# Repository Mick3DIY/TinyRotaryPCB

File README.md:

<picture>
    
</picture>

# TinyRotaryPCB

A tiny PCB (with surface resistors) for the BOURNS PEC11R rotary encoder.

## Printed Circuit Board (PCB) :

As part of an educational project, the schematic and PCB are made with [KiCad](https://www.kicad.org) version 9 ([kicad](kicad/) folder).

:bulb: All important parameters are stored in the schematic/PCB editors **text variables** (common project variables).

The TinyRotaryPCB itself with the rotary encoder (in reverse side for panel mount), dimensions (mm) :

The panelization option (2x2 boards as separate project) was generated with the KiCad plugin [KiKit](https://github.com/yaqwsx/KiKit), dimensions (mm) in [kicad/panel](kicad/panel/) folder :

If you want a quick and affordable manufacturer for your next electronic project, get a unique 10€ coupon code in <ins>your first order</ins> in [AISLER](https://aisler.net) with my referral code : `MakeInEurope-ECYPW` :heart:

Big thanks to [AISLER](https://aisler.net) PCB manufacturer :eu:

## Code :

The shell script to easily generate panels (in [kicad](kicad/) folder)… :laughing:

```shell
#!/bin/bash
# TinyRotaryPCB with KiCad and KiKit plugin for PCB panelization
# GitHub project : https://github.com/Mick3DIY/TinyRotaryPCB
# KiCad documentation : https://www.kicad.org
# KiKit plugin documentation : https://github.com/yaqwsx/KiKit

# Input and output files
INPUT_FILE="TinyRotaryPCB.kicad_pcb"
OUTPUT_DIR="panel"
OUTPUT_FILE="${OUTPUT_DIR}/TinyRotaryPCB_panel.kicad_pcb"

# Layout parameters, by default 2x2 -> panelize.sh <rows> <cols> parameters
LAYOUT_ROWS="${1:-2}"
LAYOUT_COLS="${2:-2}"
LAYOUT_SPACE="2mm"

# Tab parameters
TAB_TYPE="fixed"
TAB_HWIDTH="2mm"
TAB_VWIDTH="2mm"
TAB_VCOUNT="2"

# Cuts parameters
CUTS="mousebites; drill: 0.5mm; spacing: 0.75mm; offset: -0.3mm; prolong: 0.5mm"

# Framing parameters
FRAME_TYPE="railstb"
FRAME_WIDTH="2mm"
FRAME_SPACE="2mm"

# Text parameters
TEXT_HEIGHT="0.8mm"
TEXT_VOFFSET_POS="1mm"
TEXT_VOFFSET_NEG="-1mm"
TEXT_JUSTIFY="hjustify: center; vjustify: center;"
POST_MILLRADIUS="1mm"

# Ensure output directory exist
mkdir -p "${OUTPUT_DIR}"

# Kikit command with all parameters
kikit panelize \
    --layout "grid; rows: ${LAYOUT_ROWS}; cols: ${LAYOUT_COLS}; space: ${LAYOUT_SPACE}" \
    --tabs "${TAB_TYPE}; hwidth: ${TAB_HWIDTH}; vwidth: ${TAB_VWIDTH}; vcount: ${TAB_VCOUNT}" \
    --cuts "${CUTS}" \
    --framing "${FRAME_TYPE}; width: ${FRAME_WIDTH}; space: ${FRAME_SPACE};" \
    --text "simple; text: {boardTitle} {boardRevision} ${LAYOUT_COLS}x${LAYOUT_ROWS}; anchor: mt; voffset: ${TEXT_VOFFSET_POS}; height: ${TEXT_HEIGHT}; ${TEXT_JUSTIFY}" \
    --text2 "simple; text: Created on {boardDate}; anchor: mb; voffset: ${TEXT_VOFFSET_NEG}; height: ${TEXT_HEIGHT}; ${TEXT_JUSTIFY}" \
    --post "millradius: ${POST_MILLRADIUS}" \
    "${INPUT_FILE}" "${OUTPUT_FILE}"

# Check if the command succeeded
if [ $? -eq 0 ]; then
    echo "Panelization successful : ${OUTPUT_FILE}"
else
    echo "Error : Panelization failed"
    exit 1
fi
```

More panelization examples in KiKit plugin documentation : https://yaqwsx.github.io/KiKit/latest/panelization/examples/

## Logic analyser with the rotary encoder :

To understand how a rotary encoder "pulses" works, it is useful to visualise it with a software/hardware logic analysers.

Here an example with the same schematic (pins A, B, SW) in [Sigrok](https://sigrok.org) and PulseView softwares :

## TODO :

- [x] Add PDF files for the schematic, PCBs (single, panelization)
- [x] Add a screenshot from the logic analyser [Sigrok](https://sigrok.org)
- [x] Add link to the Elektor Ebook "Logic Analyzers in Practice" from Jörg Rippel
- [ ] Add picture of the PCB boards from AISLER
- [ ] Add more files and examples, any ideas ? :laughing:

## Documentation :

BOURNS PEC11R Series 12 mm incremental rotary encoder (PEC11R-4220F-S0024) :
* https://www.bourns.com/resources/rohs/encoders/contacting-encoders
* https://www.bourns.com/docs/product-datasheets/pec11r.pdf

Sigrok, PulseView softwares, all cross-platform : https://sigrok.org :clap:

Elektor Ebook "Logic Analyzers in Practice" from Jörg Rippel :
* https://www.elektor.fr/products/logic-analyzers-in-practice-e-book :ok_hand:

> [!NOTE]
> Big thanks to the open-source, [KiCad](https://www.kicad.org), [KiKit](https://github.com/yaqwsx/KiKit) and plugins communities. :heart:

Happy soldering & have fun ! :partying_face:

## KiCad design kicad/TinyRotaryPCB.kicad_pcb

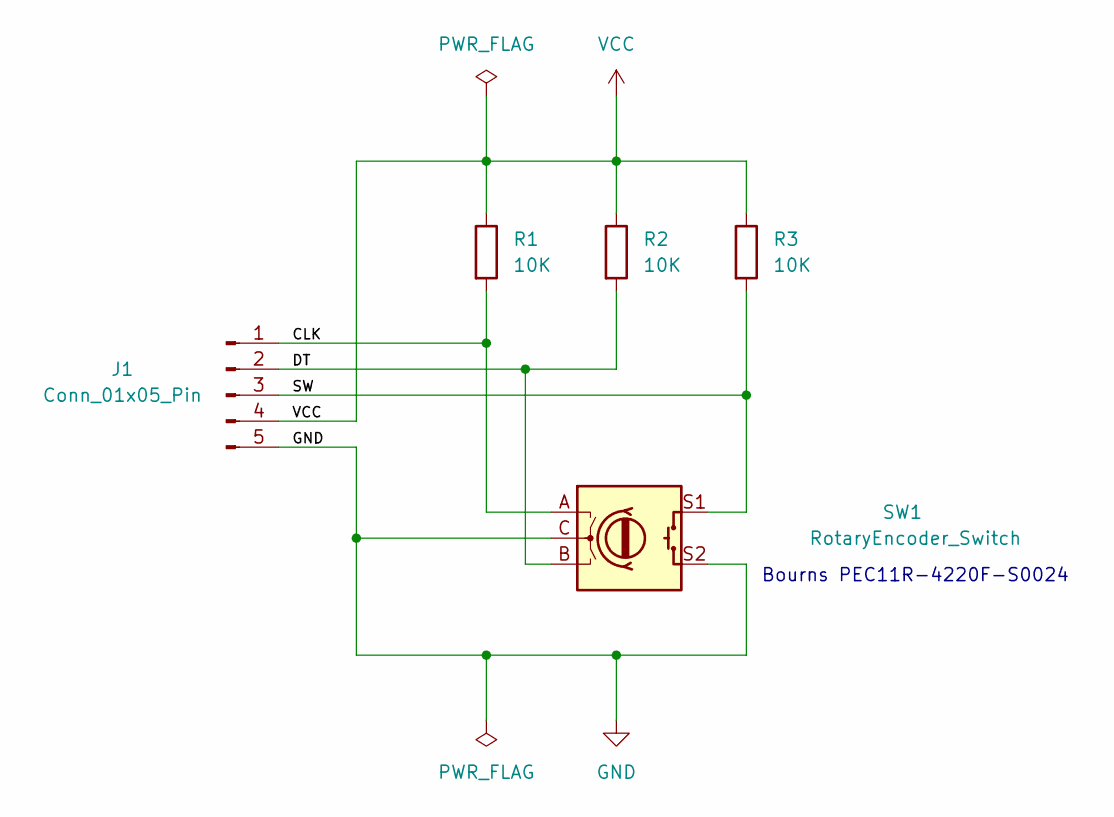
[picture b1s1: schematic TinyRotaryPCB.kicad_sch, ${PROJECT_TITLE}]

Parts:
J1: Conn_01x05_Pin; PinHeader_1x05_P2.54mm_Horizontal_Without_Silkscreen
R1, R2, R3: 10K; R_1206_3216Metric_Pad1.30x1.75mm_HandSolder
SW1: RotaryEncoder_Switch; RotaryEncoder_Bourns_Vertical_PEC11R-4xxxF-Sxxxx

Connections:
/CLK: J1.1, R1.2, SW1.A
/DT: J1.2, R2.2, SW1.B
/SW: J1.3, R3.2, SW1.S1
GND: J1.5, SW1.C, SW1.S2
VCC: J1.4, R1.1, R2.1, R3.1

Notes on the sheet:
Bourns PEC11R-4220F-S0024

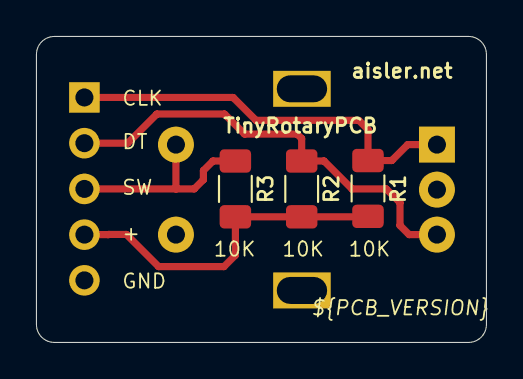
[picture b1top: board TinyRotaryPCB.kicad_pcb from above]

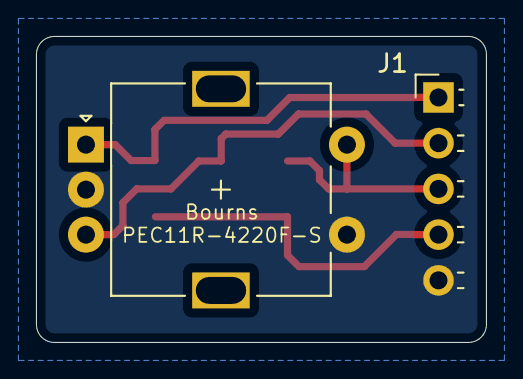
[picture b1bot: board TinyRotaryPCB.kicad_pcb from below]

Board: 2 copper layers, 25.0 x 17.0 mm, 5 parts (2 on the bottom side), 5 nets.

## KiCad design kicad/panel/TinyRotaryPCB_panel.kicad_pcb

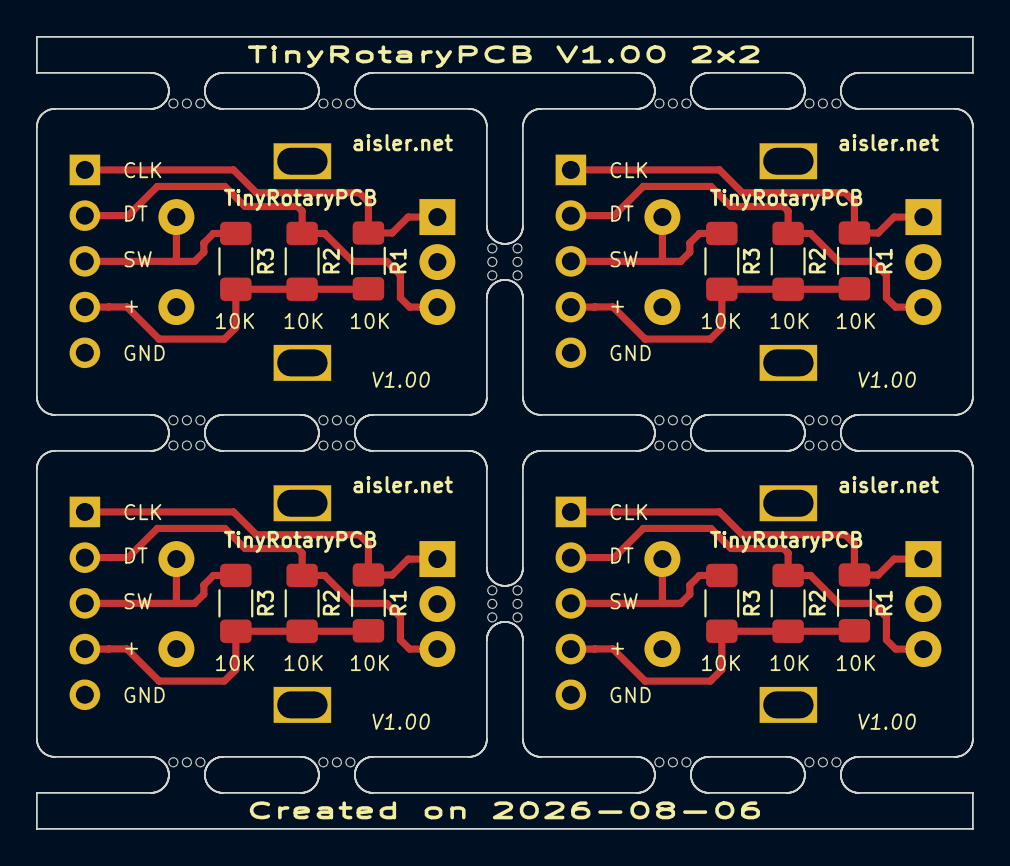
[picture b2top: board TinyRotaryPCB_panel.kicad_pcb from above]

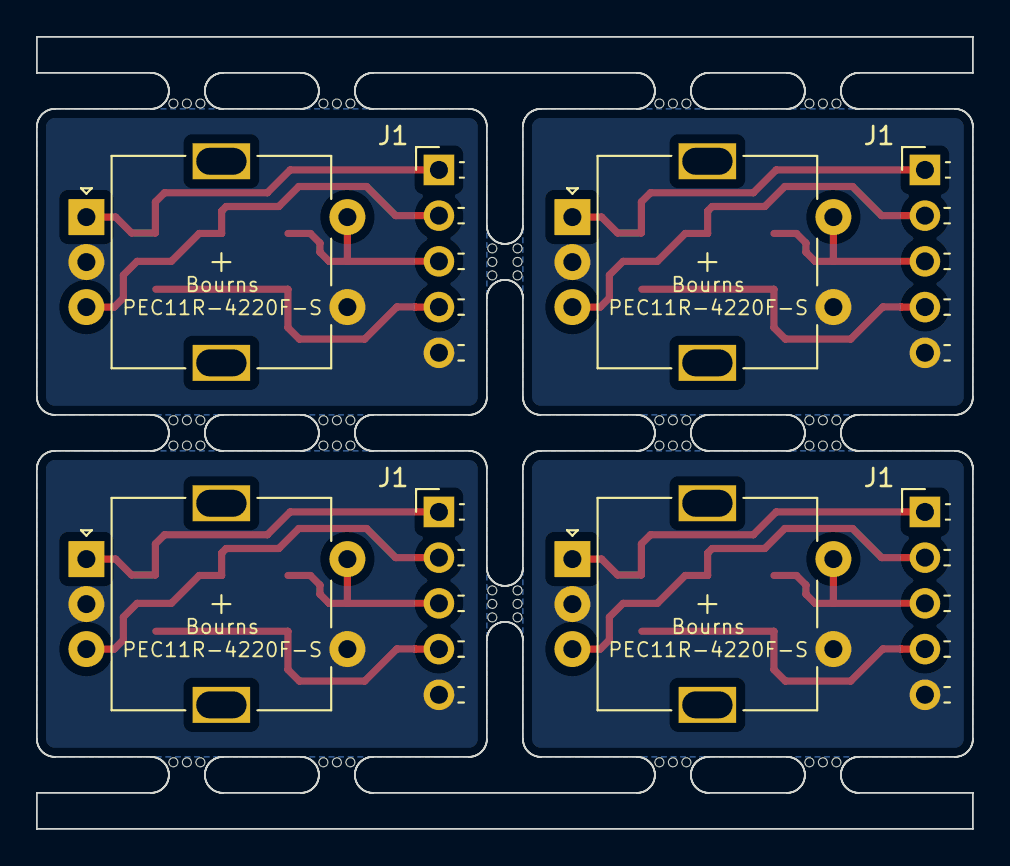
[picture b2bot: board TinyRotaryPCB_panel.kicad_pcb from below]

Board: 2 copper layers, 52.0 x 44.0 mm, 80 parts (8 on the bottom side), 20 nets.

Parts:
J1, J1#2, J1#3, J1#4: Conn_01x05_Pin; PinHeader_1x05_P2.54mm_Horizontal_Without_Silkscreen
KiKit_MB_1_2, KiKit_MB_1_3, KiKit_MB_1_4, KiKit_MB_2_2, KiKit_MB_2_3, KiKit_MB_2_4, KiKit_MB_3_2, KiKit_MB_3_3, KiKit_MB_3_4, KiKit_MB_4_2, KiKit_MB_4_3, KiKit_MB_4_4, KiKit_MB_5_2, KiKit_MB_5_3, KiKit_MB_5_4, KiKit_MB_6_2, KiKit_MB_6_3, KiKit_MB_6_4, KiKit_MB_7_2, KiKit_MB_7_3, KiKit_MB_7_4, KiKit_MB_8_2, KiKit_MB_8_3, KiKit_MB_8_4, KiKit_MB_9_2, KiKit_MB_9_3, KiKit_MB_9_4, KiKit_MB_10_2, KiKit_MB_10_3, KiKit_MB_10_4, KiKit_MB_11_2, KiKit_MB_11_3, KiKit_MB_11_4, KiKit_MB_12_2, KiKit_MB_12_3, KiKit_MB_12_4, KiKit_MB_13_2, KiKit_MB_13_3, KiKit_MB_13_4, KiKit_MB_14_2, KiKit_MB_14_3, KiKit_MB_14_4, KiKit_MB_15_2, KiKit_MB_15_3, KiKit_MB_15_4, KiKit_MB_16_2, KiKit_MB_16_3, KiKit_MB_16_4, KiKit_MB_17_2, KiKit_MB_17_3, KiKit_MB_17_4, KiKit_MB_18_2, KiKit_MB_18_3, KiKit_MB_18_4, KiKit_MB_19_2, KiKit_MB_19_3, KiKit_MB_19_4, KiKit_MB_20_2, KiKit_MB_20_3, KiKit_MB_20_4: NPTH
R1, R1#2, R1#3, R1#4, R2, R2#2, R2#3, R2#4, R3, R3#2, R3#3, R3#4: 10K; R_1206_3216Metric_Pad1.30x1.75mm_HandSolder
SW1, SW1#2, SW1#3, SW1#4: RotaryEncoder_Switch; RotaryEncoder_Bourns_Vertical_PEC11R-4xxxF-Sxxxx

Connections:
Board_0-/CLK: J1#4.1, R1.2, SW1#2.A
Board_0-/DT: J1#4.2, R2.2, SW1#2.B
Board_0-/SW: J1#4.3, R3#2.2, SW1#2.S1
Board_0-GND: J1#4.5, SW1#2.C, SW1#2.S2
Board_0-VCC: J1#4.4, R1.1, R2.1, R3#2.1
Board_1-/CLK: J1#2.1, R1#3.2, SW1#3.A
Board_1-/DT: J1#2.2, R2#4.2, SW1#3.B
Board_1-/SW: J1#2.3, R3#3.2, SW1#3.S1
Board_1-GND: J1#2.5, SW1#3.C, SW1#3.S2
Board_1-VCC: J1#2.4, R1#3.1, R2#4.1, R3#3.1
Board_2-/CLK: J1#3.1, R1#2.2, SW1#4.A
Board_2-/DT: J1#3.2, R2#3.2, SW1#4.B
Board_2-/SW: J1#3.3, R3#4.2, SW1#4.S1
Board_2-GND: J1#3.5, SW1#4.C, SW1#4.S2
Board_2-VCC: J1#3.4, R1#2.1, R2#3.1, R3#4.1
Board_3-/CLK: J1.1, R1#4.2, SW1.A
Board_3-/DT: J1.2, R2#2.2, SW1.B
Board_3-/SW: J1.3, R3.2, SW1.S1
Board_3-GND: J1.5, SW1.C, SW1.S2
Board_3-VCC: J1.4, R1#4.1, R2#2.1, R3.1
